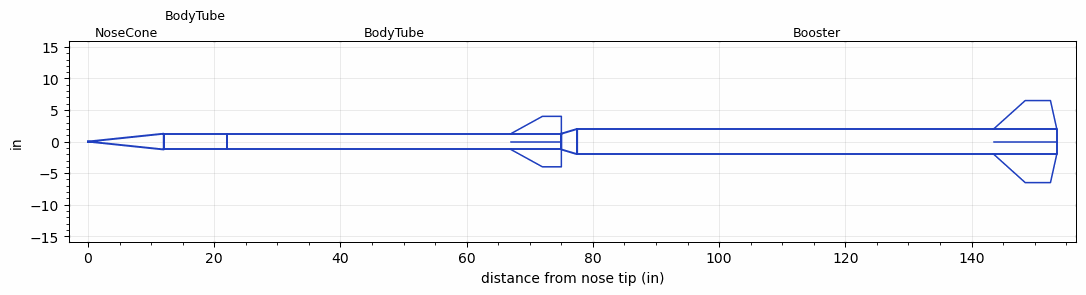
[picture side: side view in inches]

<RASAeroDocument>
 <FileVersion>2</FileVersion>
 <RocketDesign>
  <NoseCone>
   <Length>12</Length>
   <Diameter>2.5</Diameter>
   <Shape>Conical</Shape>
   <BluntRadius>0.06</BluntRadius>
   <Location>0</Location>
  </NoseCone>
  <BodyTube>
   <Length>10</Length>
   <Diameter>2.5</Diameter>
   <Location>12</Location>
  </BodyTube>
  <BodyTube>
   <Length>53</Length>
   <Diameter>2.5</Diameter>
   <Location>22</Location>
   <Fin>
    <Count>4</Count>
    <Chord>8</Chord>
    <Span>2.75</Span>
    <SweepDistance>5</SweepDistance>
    <TipChord>3</TipChord>
    <Thickness>0.1875</Thickness>
    <LERadius>0.01</LERadius>
    <Location>8</Location>
    <AirfoilSection>Hexagonal</AirfoilSection>
    <FX1>0.5</FX1>
    <FX3>0.5</FX3>
   </Fin>
  </BodyTube>
  <Booster>
   <Length>76</Length>
   <Diameter>4</Diameter>
   <InsideDiameter>2.5</InsideDiameter>
   <Location>75</Location>
   <ShoulderLength>2.5</ShoulderLength>
   <Fin>
    <Count>4</Count>
    <Chord>10</Chord>
    <Span>4.5</Span>
    <SweepDistance>5</SweepDistance>
    <TipChord>4</TipChord>
    <Thickness>0.1875</Thickness>
    <LERadius>0.01</LERadius>
    <Location>10</Location>
    <AirfoilSection>Hexagonal</AirfoilSection>
    <FX1>0.75</FX1>
    <FX3>0.75</FX3>
   </Fin>
  </Booster>
  <Surface>Rough Camouflage Paint</Surface>
  <ModifiedBarrowman>False</ModifiedBarrowman>
  <Turbulence>False</Turbulence>
  <UseBooster1>True</UseBooster1>
  <UseBooster2>False</UseBooster2>
 </RocketDesign>
 <LaunchSite>
  <Altitude>15000</Altitude>
  <Pressure>29.92</Pressure>
  <RodAngle>2</RodAngle>
  <RodLength>3.28</RodLength>
  <Temperature>59</Temperature>
  <WindSpeed>4.47</WindSpeed>
 </LaunchSite>
 <Recovery>
  <Altitude1>0</Altitude1>
  <Altitude2>0</Altitude2>
  <DeviceType1>None</DeviceType1>
  <DeviceType2>None</DeviceType2>
  <Event1>False</Event1>
  <Event2>False</Event2>
  <Size1>0</Size1>
  <Size2>0</Size2>
  <EventType1>None</EventType1>
  <EventType2>None</EventType2>
  <CD1>0</CD1>
  <CD2>0</CD2>
 </Recovery>
 <SimulationList>
  <Simulation>
   <SustainerEngine>N3358BP  (Polaris)</SustainerEngine>
   <SustainerLaunchWt>22</SustainerLaunchWt>
   <SustainerNozzleDiameter>2.4</SustainerNozzleDiameter>
   <SustainerCG>42.73</SustainerCG>
   <SustainerIgnitionDelay>10</SustainerIgnitionDelay>
   <Booster1Engine>O6898BPNC  (Polaris)</Booster1Engine>
   <Booster1LaunchWt>72</Booster1LaunchWt>
   <Booster1SeparationDelay>0</Booster1SeparationDelay>
   <Booster1IgnitionDelay>0</Booster1IgnitionDelay>
   <Booster1CG>97.6</Booster1CG>
   <Booster1NozzleDiameter>3.75</Booster1NozzleDiameter>
   <IncludeBooster1>True</IncludeBooster1>
   <Booster2Delay>0</Booster2Delay>
   <IncludeBooster2>False</IncludeBooster2>
   <TimetoApogee>250.994</TimetoApogee>
   <MaxAltitude>937184</MaxAltitude>
   <MaxVelocity>7672.652</MaxVelocity>
  </Simulation>
 </SimulationList>
</RASAeroDocument>
